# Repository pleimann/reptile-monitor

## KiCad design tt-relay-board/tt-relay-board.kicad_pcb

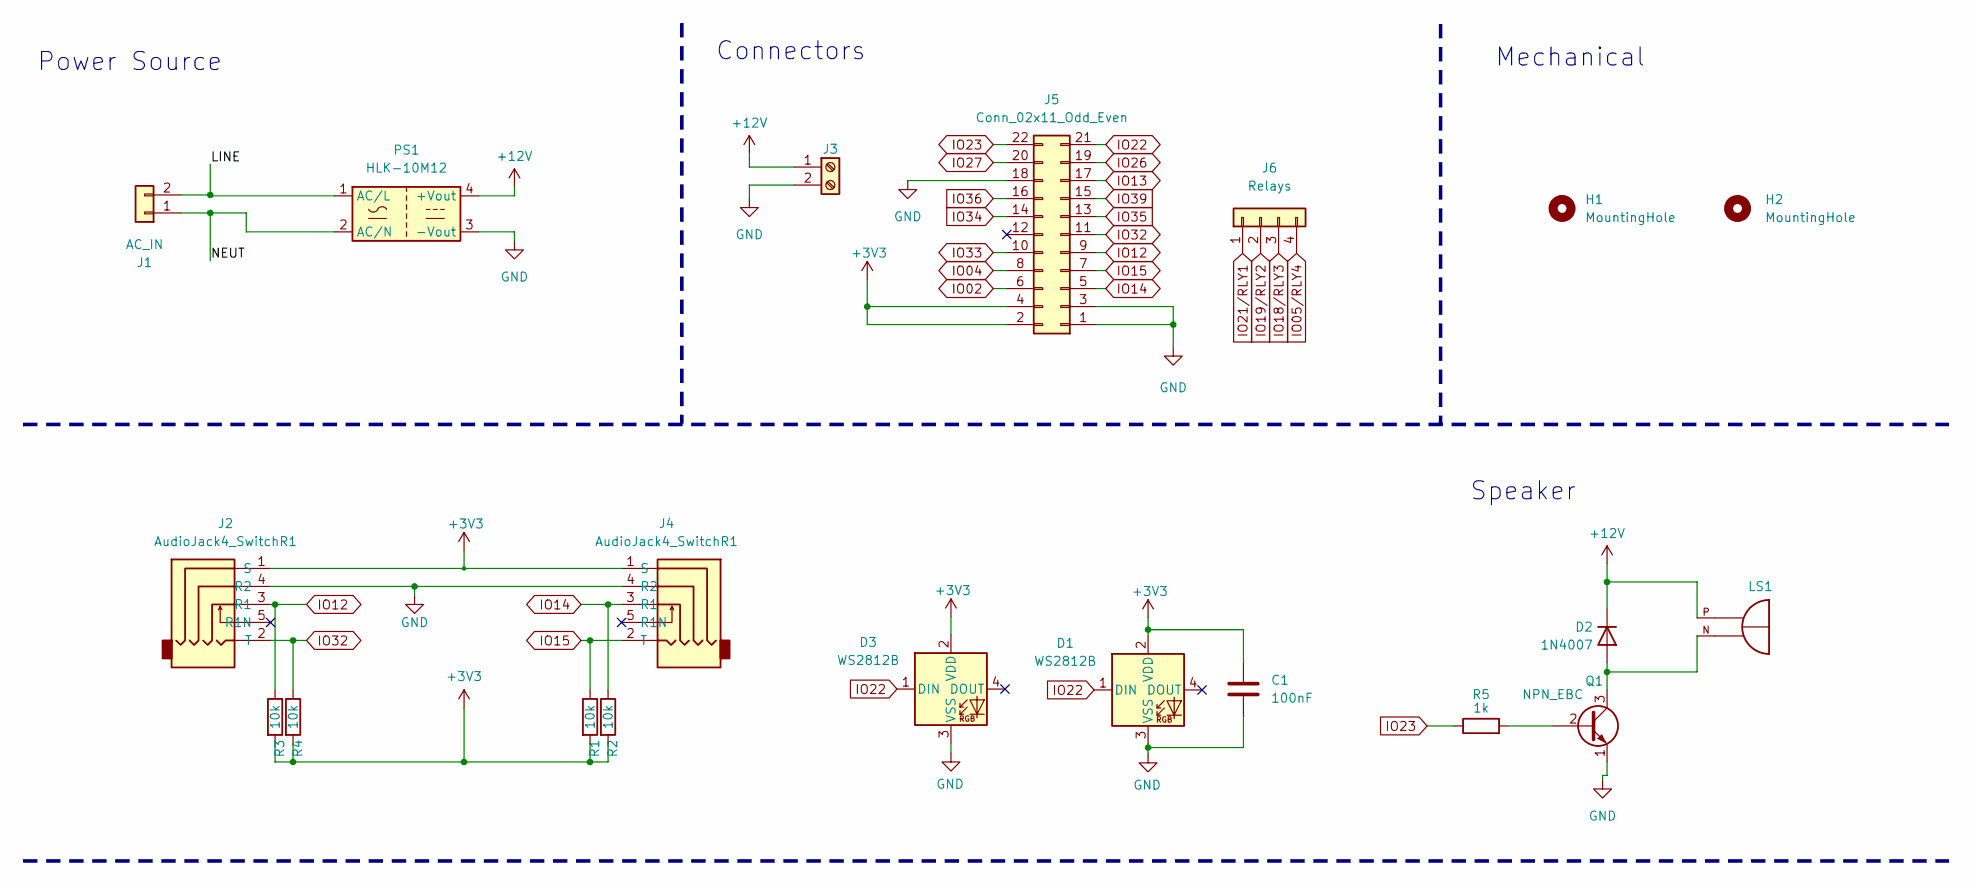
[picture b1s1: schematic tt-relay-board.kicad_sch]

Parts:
C1: 100nF; C_0603_1608Metric_Pad1.08x0.95mm_HandSolder
D1: WS2812B; LED_D5.0mm-4_RGB_Wide_Pins
D2: 1N4007; D_SOD-123F
D3: WS2812B; LED_WS2812B_PLCC4_5.0x5.0mm_P3.2mm
H1, H2: MountingHole; MountingHole_4mm
J1: AC_IN; SolderWire-0.75sqmm_1x02_P7mm_D1.25mm_OD3.5mm_Relief
J2, J4: AudioJack4_SwitchR1; Korean Hroparts Elec PJ-227-5A; LCSC Part C145819
J3: Screw_Terminal_01x02; SHDR2W110P0X500_1X2_1000X1120X
J5: Conn_02x11_Odd_Even; PinSocket_2x11_P2.54mm_Vertical
J6: Relays
LS1: XDCR_KSSG1201-16; mouser part number 539-AST7525MATRQ; digikey description AUDIO MAGNETIC XDCR 2.5-4.5V SMD
PS1: HLK-10M12; Converter_ACDC_HiLink_HLK-10Mxx
Q1: NPN_EBC; SOT-23
R1, R2, R3, R4: 10k; R_0603_1608Metric_Pad0.98x0.95mm_HandSolder
R5: 1k; R_0603_1608Metric_Pad0.98x0.95mm_HandSolder

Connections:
+3V3: C1.1, D1.2 (VDD), D3.2 (VDD), J2.1 (S), J4.1 (S), J5.2, J5.4, R1.2, R2.2, R3.2, R4.2
+12V: D2.1 (K), J3.1, LS1.P, PS1.4 (+Vout)
/LINE: J1.2, PS1.1 (AC/L)
/NEUT: J1.1, PS1.2 (AC/N)
GND: C1.2, D1.3 (VSS), D3.3 (VSS), J2.4 (R2), J3.2, J4.4 (R2), J5.1, J5.3, J5.18, PS1.3 (-Vout), Q1.1 (E)
IO02: J5.6
IO04: J5.8
IO12: J2.3 (R1), J5.9, R3.1
IO13: J5.17
IO14: J4.3 (R1), J5.5, R2.1
IO15: J4.2 (T), J5.7, R1.1
IO22: D1.1 (DIN), D3.1 (DIN), J5.21
IO23: J5.22, R5.1
IO26: J5.19
IO27: J5.20
IO32: J2.2 (T), J5.11, R4.1
IO33: J5.10
IO34: J5.14
IO35: J5.13
IO36: J5.16
IO39: J5.15
unnamed: D2.2 (A), LS1.N, Q1.3 (C)
unnamed: Q1.2 (B), R5.2

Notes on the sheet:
Power Source
Speaker
Mechanical
Connectors

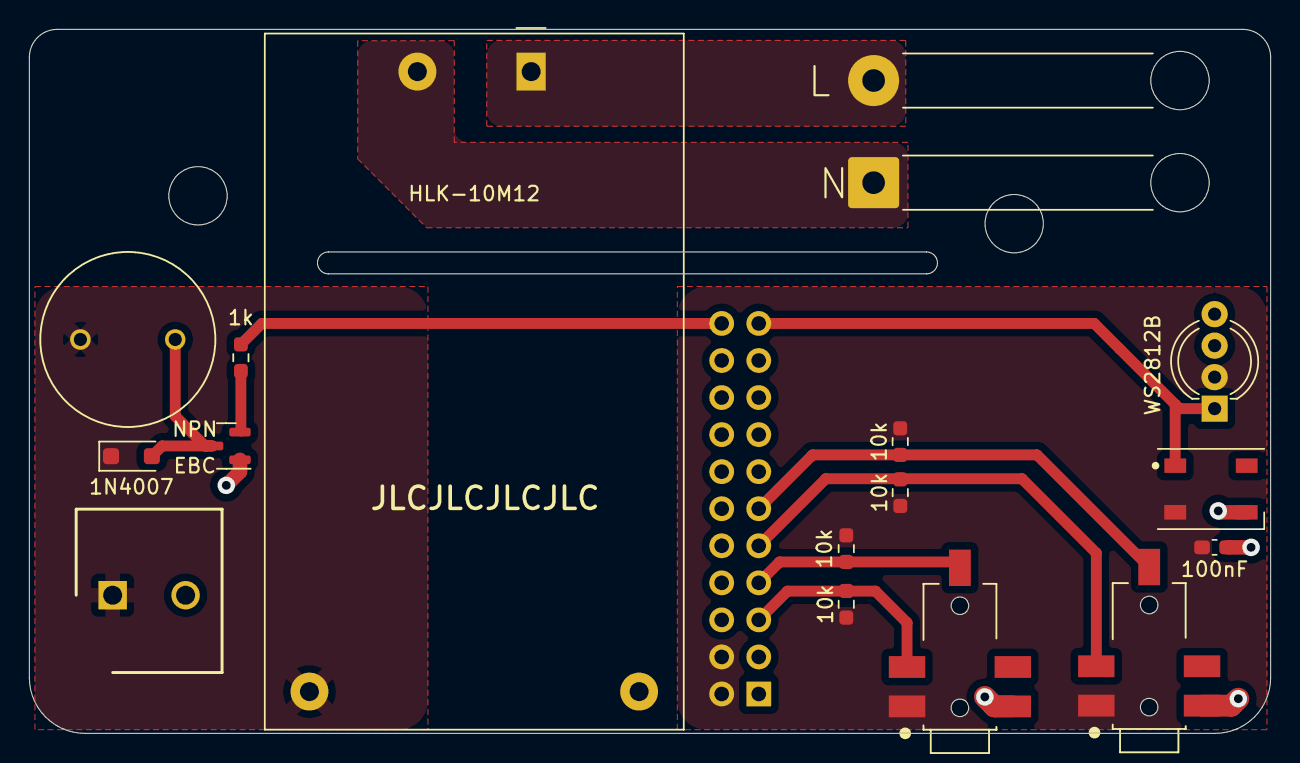
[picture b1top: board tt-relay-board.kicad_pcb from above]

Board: 2 copper layers, 85.1 x 48.3 mm, 19 parts (1 on the bottom side), 13 nets.

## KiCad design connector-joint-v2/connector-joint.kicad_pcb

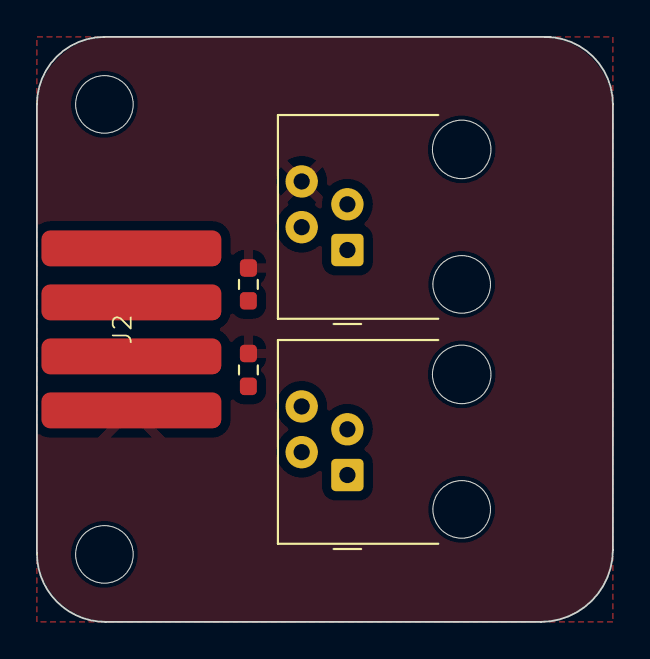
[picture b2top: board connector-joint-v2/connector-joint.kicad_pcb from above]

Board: 2 copper layers, 32.0 x 32.5 mm, 7 parts (0 on the bottom side), 4 nets, no tracks yet.

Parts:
H1, H2: MountingHole; MountingHole_3.2mm_M3
J2: Conn_01x04; SolderPad_x4
J4, J5: 4P4C; RJ9_Evercom_5301-440xxx_Horizontal
R1, R2: R_US; R_0603_1608Metric_Pad0.98x0.95mm_HandSolder

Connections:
+3V3: J2.4 (3V3), J4.3, J5.2
GND: J2.3 (GND), J4.2, J5.3, R2.2
unnamed: J2.1 (DATA), J4.4, R1.1, R2.1
unnamed: J2.2 (DATA), J4.1, J5.4, R1.2

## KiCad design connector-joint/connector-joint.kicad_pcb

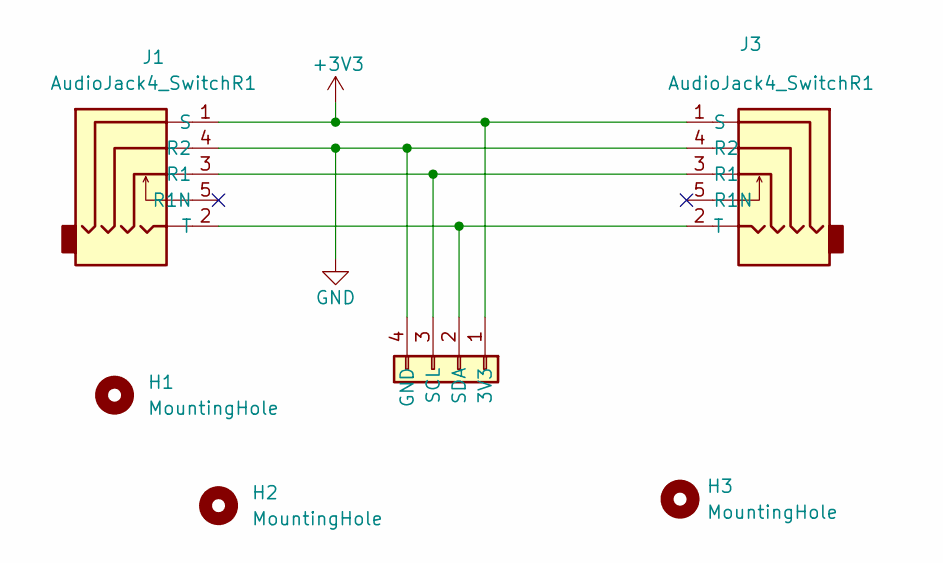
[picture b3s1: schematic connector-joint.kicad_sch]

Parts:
H1, H2, H3: MountingHole; MountingHole_3.2mm_M3
J1, J3: AudioJack4_SwitchR1; Korean Hroparts Elec PJ-227-5A; LCSC Part C145819
J2: Conn_01x04; SolderWire-0.15sqmm_1x04_P4mm_D0.5mm_OD1.5mm

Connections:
+3V3: J1.1 (S), J2.1, J3.1 (S)
GND: J1.4 (R2), J2.4, J3.4 (R2)
unnamed: J1.2 (T), J2.2, J3.2 (T)
unnamed: J1.3 (R1), J2.3, J3.3 (R1)

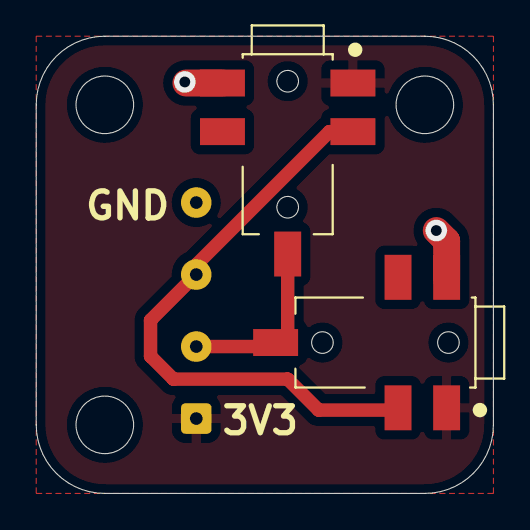
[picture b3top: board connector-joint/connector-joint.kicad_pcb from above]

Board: 2 copper layers, 25.4 x 25.4 mm, 6 parts (0 on the bottom side), 4 nets.

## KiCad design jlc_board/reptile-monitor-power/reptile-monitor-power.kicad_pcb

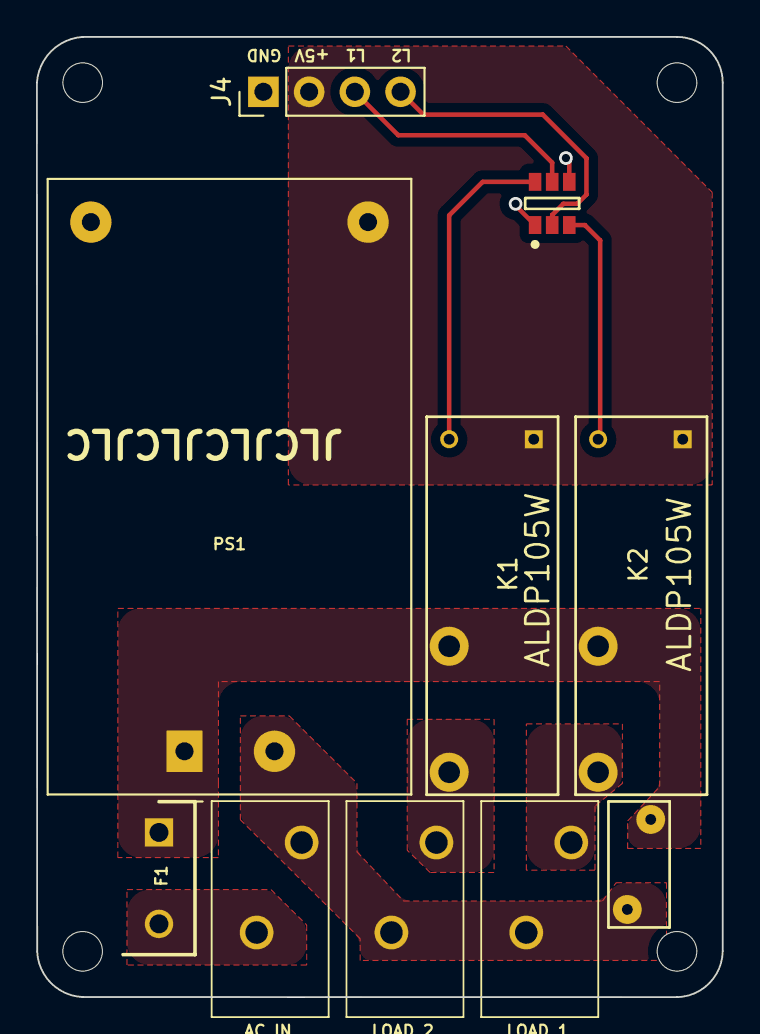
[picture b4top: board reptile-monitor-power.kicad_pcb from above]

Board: 4 copper layers, 38.1 x 53.3 mm, 14 parts (0 on the bottom side), 11 nets.

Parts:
F1: 39208000440; TO508P400X850X850-2P
J1: AC_IN; TE Connectivity PC Terminal Block 128340212
J2: LOAD_2; TE Connectivity PC Terminal Block 128340212
J3: LOAD_1; TE Connectivity PC Terminal Block 128340212
J4: POWER CONN; PinHeader_1x04_P2.54mm_Vertical
K1, K2: ALDP105W; Panasonic-ALDP105W-Manufacturer_Recommended
PS1: HLK-PM01; Converter_ACDC_HiLink_HLK-PMxx
REF1, REF1#2, REF1#3, REF1#4: MountingHole_2.2mm_M2_ISO7380
RV1: Varistor; RV_Disc_D7mm_W3.4mm_P5mm
U1: NUD3105DMT1G; ON_Semi-318F-0-0-0

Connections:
+5V: J4.2, K1.1, K2.1, PS1.4 (+Vout)
/FUSED_AC_L: F1.1, K1.3 (COM), K2.3 (COM), PS1.1 (AC/L), RV1.2
/LOAD1: J3.2, K2.2 (NO)
/LOAD2: J2.2, K1.2 (NO)
GND: J4.1, PS1.3 (-Vout), U1.1 (1_Source), U1.4 (2_Source)
L1: J4.3, U1.5 (2_Gate)
L2: J4.4, U1.2 (1_Gate)
LINE: F1.2, J1.1
NEUT: J1.2, J2.1, J3.1, PS1.2 (AC/N), RV1.1
RLY1: K2.4, U1.3 (2_Drain)
RLY2: K1.4, U1.6 (1_Drain)

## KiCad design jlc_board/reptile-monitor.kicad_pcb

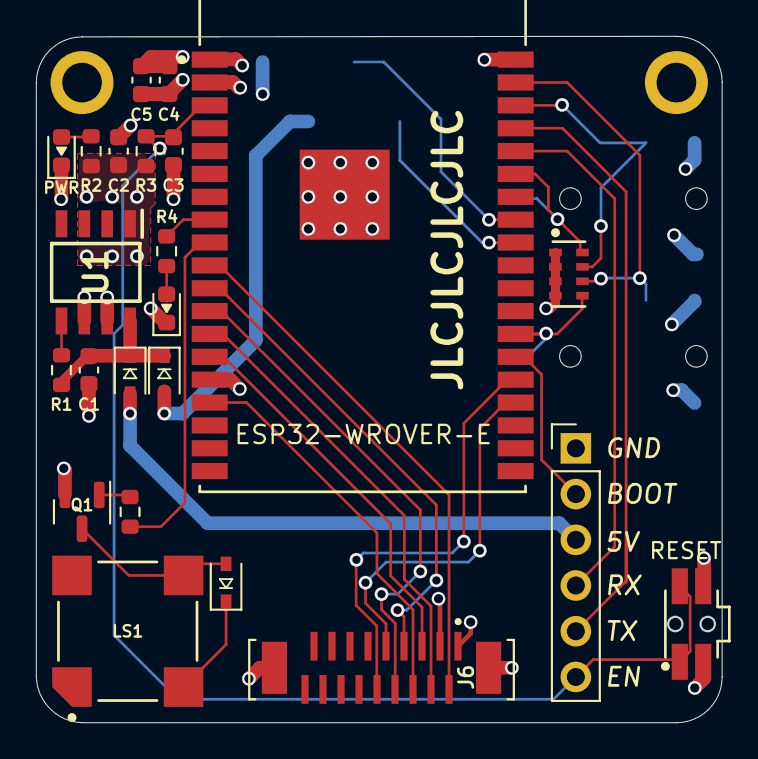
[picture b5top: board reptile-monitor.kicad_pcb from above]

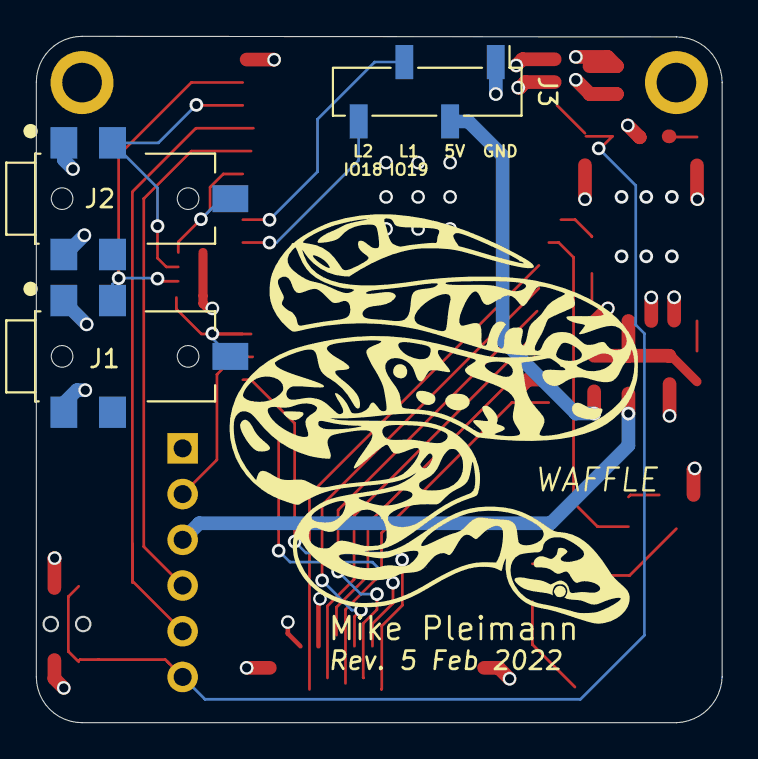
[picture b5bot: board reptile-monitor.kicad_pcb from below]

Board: 4 copper layers, 38.1 x 38.1 mm, 29 parts (4 on the bottom side), 31 nets.

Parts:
C1, C2: 1u; C_0603_1608Metric
C3, C5: 100n; C_0603_1608Metric
C4: 22u; C_0603_1608Metric
D1: PWR; LED_0603_1608Metric
D2: 32; LED_0603_1608Metric
D3, D4, D5: 1N4007; D_SOD-323
H1, H2: MountingHole; MountingHole_2.2mm_M2_ISO7380_Pad
J1, J2: AudioJack4_SwitchR1; Korean Hroparts Elec PJ-227-5A
J3: PWR CONN; PinSocket_1x04_P2.54mm_Vertical_SMD_Pin1Left
J4: UART; PinHeader_1x06_P2.54mm_Vertical
J6: 18-Lead FPC 0.5 mm - Vertical; TE_1-1734742-8
LS1: AST7525MATRQ; Mallory_Sonalert_Products_Inc-AST7525MATRQ-0-0-MFG
MD1: ESP32-WROVER-E; Espressif_Systems-ESP32-WROVER-0-0-MFG
Q1: Q_NPN_BEC; SOT-23
R1, R2, R3: 10k; R_0603_1608Metric
R4: 1k; R_0603_1608Metric
R5: 1K; R_0603_1608Metric
RN1: 10k; Panasonic-EXB-V8V103JV-0
SW1: RESET; Panasonic-EVQ-P7A01P
U1: AP2112M-3.3; SOIC127P600X170-8N
WAFFLE: LOGO

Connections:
+3V3: C2.2, C4.1, C5.1, J1.1 (S), J2.1 (S), J6.1, MD1.2 (VDD33), R2.1, R3.2, RN1.1 (R1.1), RN1.2 (R2.1), RN1.3 (R3.1), RN1.4 (R4.1), U1.1 (VOUT)
+5V: C1.1, D4.1 (K), D5.1 (K), R1.2, U1.8 (VIN)
/LED: MD1.8 (IO32), R4.2
/PWR_EN: R1.1, U1.5 (EN)
BK_LT: J6.2, MD1.10 (IO25)
BOOT: J4.2, MD1.25 (IO0)
BUZZER: MD1.9 (IO33), R5.1
DS_0: J1.3 (R1), MD1.37 (IO23), RN1.6 (R3.2)
DS_DATA: J1.2 (T), MD1.26 (IO4), RN1.5 (R4.2)
EN: C3.2, J4.6, MD1.3 (EN), R3.1, SW1.1, SW1.1'
GND: C1.2, C2.1, C3.1, C4.2, C5.2, D1.1 (K), D2.1 (K), H1.1, H2.1, J1.4 (R2), J2.4 (R2), J3.1, J4.1, J6.3, J6.S1 (SHIELD), J6.S2 (SHIELD), MD1.1 (GND), MD1.15 (GND), MD1.38 (GND), MD1.39 (GND), Q1.2 (E), SW1.2, SW1.2', U1.6 (GND_1), U1.7 (GND_2)
L1: J3.3, MD1.31 (IO19)
L2: J3.4, MD1.30 (IO18)
unnamed: D1.2 (A), R2.2
unnamed: D2.2 (A), R4.1
unnamed: D3.2 (A), LS1.4 (-), Q1.3 (C)
unnamed: D5.2 (A), J3.2
unnamed: D4.2 (A), J4.3
unnamed: Q1.1 (B), R5.2
RXD0: J4.4, MD1.34 (RXD0)
SCL0: J2.3 (R1), MD1.36 (IO22), RN1.7 (R2.2)
SDA0: J2.2 (T), MD1.33 (IO21), RN1.8 (R1.2)
SD_CS: J6.10, MD1.24 (IO2)
SPI_SCK: J6.4, MD1.13 (IO14)
SPI_SDI: J6.5, MD1.14 (IO12)
SPI_SDO: J6.6, MD1.16 (IO13)
TFT_CS: J6.9, MD1.23 (IO15)
TFT_DC: J6.7, MD1.11 (IO26)
TFT_RST: J6.8, MD1.12 (IO27)
TXD0: J4.5, MD1.35 (TXD0)
VDD: D3.1 (K), LS1.3 (+)

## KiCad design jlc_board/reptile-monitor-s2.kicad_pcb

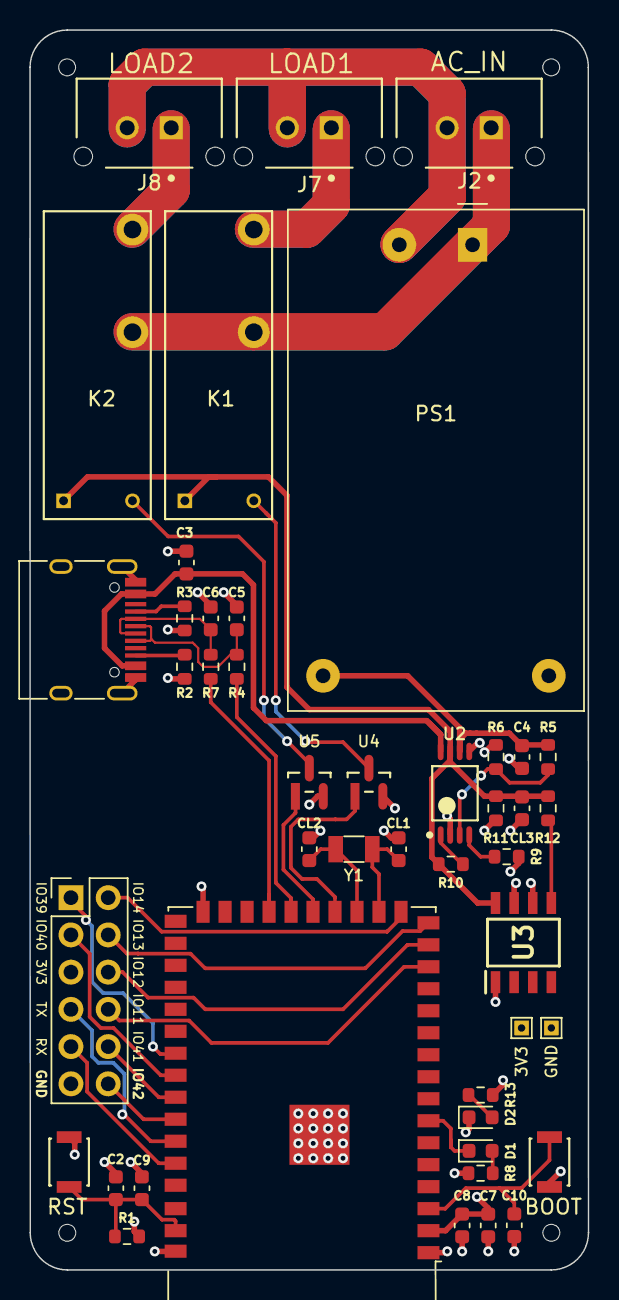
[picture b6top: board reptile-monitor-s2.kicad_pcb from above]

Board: 4 copper layers, 38.1 x 84.6 mm, 45 parts (0 on the bottom side), 40 nets.

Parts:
C2, C3, C4, C7, C9, C10: 0.1u; C_0603_1608Metric
C5, C6: 20p; C_0603_1608Metric
C8: 22u; C_0603_1608Metric
CL1, CL2: 20p; C_0603_1608Metric
CL3: 10u; C_0603_1608Metric
D1, D2: LED; LED_0603_1608Metric
J1: USB_C_Receptacle_USB2.0; USB_C_Receptacle_HRO_TYPE-C-31-M-12
J2: AC_IN; Molex-43650-0215-0-0-MFG
J3: Conn_01x08; PinHeader_2x06_P2.54mm_Vertical
J7: LOAD1; Molex-43650-0215-0-0-MFG
J8: LOAD2; Molex-43650-0215-0-0-MFG
K1, K2: ALDP105W; Panasonic-ALDP105W-Manufacturer_Recommended
PS1: HLK-PM01; Converter_ACDC_HiLink_HLK-PMxx
R1, R10, R11, R12: 10k; R_0603_1608Metric
R2, R3: 5.1k; R_0603_1608Metric
R4, R7: 22r; R_0603_1608Metric
R5: 2.2k; R_0603_1608Metric
R6: 1k; R_0603_1608Metric
R8, R13: 100r; R_0603_1608Metric
R9: 500r; R_0603_1608Metric
SW1: RST; Omron-B3U-1000P-MFG
SW2: BOOT; Omron-B3U-1000P-MFG
TP1: 3V3; TestPoint_THTPad_1.0x1.0mm_Drill0.5mm
TP3: GND; TestPoint_THTPad_1.0x1.0mm_Drill0.5mm
U1: ESP32-S2-WROVER
U2: TPS2112PW; Texas_Instruments-TPS2112PW
U3: AP2112K-3.3; SOIC127P600X170-8N
U4, U5: MDC3105LT1G; ON_Semiconductor-318-08-01_2018-AS
Y1: 32.768KHz 12.5p; Crystal_SMD_3215-2Pin_3.2x1.5mm

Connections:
+3V3: C7.1, C8.1, J3.5, R1.1, R13.1, TP1.1, U1.2 (3V3), U3.1 (VOUT)
+5V: CL3.1, K1.1, K2.1, R10.2, R11.2, R12.2, U2.7 (OUT), U3.8 (VIN)
/AC_L: J2.1, K1.3 (COM), K2.3 (COM), PS1.1 (AC/L)
/AC_N: J2.2, J7.2, J8.2, PS1.2 (AC/N)
/EN: C2.1, C9.1, R1.2, SW1.1, U1.41 (EN)
/IO0: C10.1, SW2.1, U1.3 (IO00)
/IO11: J3.8, U1.14 (IO11)
/IO12: J3.6, U1.15 (IO12)
/IO13: J3.4, U1.16 (IO13)
/IO14: J3.2, U1.17 (IO14)
/IO15: CL1.1, U1.18 (IO15), Y1.2
/IO16: CL2.1, U1.19 (IO16), Y1.1
/IO17: U1.20 (IO17), U4.1 (Vin)
/IO18: U1.21 (IO18), U5.1 (Vin)
/IO39: J3.1, U1.33 (IO39)
/IO40: J3.3, U1.34 (IO40)
/IO41: J3.10, U1.35 (IO41)
/IO42: J3.12, U1.36 (IO42)
/LOAD1: J7.1, K1.2 (NO)
/LOAD2: J8.1, K2.2 (NO)
/PWR_SRC: R10.1, U2.1 (STAT)
/RXD0: J3.9, U1.38 (RXD0)
/TXD0: J3.7, U1.37 (TXD0)
/USB_D+: C5.2, J1.A6 (D+), J1.B6 (D+), R4.1
/USB_D-: C6.1, J1.A7 (D-), J1.B7 (D-), R7.1
GND: C2.2, C3.2, C4.2, C5.1, C6.2, C7.2, C8.2, C9.2, C10.2, CL1.2, CL2.2, CL3.2, D2.1 (K), J1.A1 (GND), J1.A12 (GND), J1.B1 (GND), J1.B12 (GND), J1.S1 (SHIELD), J3.11, PS1.3 (-Vout), R2.2, R3.2, R6.2, R8.2, R9.1, R11.1, SW1.2, SW2.2, TP3.1, U1.1 (GND), U1.26 (GND), U1.42 (GND), U1.43 (GND), U2.2 (~EN~), U2.5 (GND), U3.6 (GND_1), U3.7 (GND_2), U4.2 (GND), U5.2 (GND)
unnamed: D1.1 (K), U1.7 (IO04)
unnamed: D1.2 (A), R8.1
unnamed: D2.2 (A), R13.2
unnamed: J1.A5 (CC1), R3.1
unnamed: J1.B5 (CC2), R2.1
unnamed: K2.4, U5.3 (Vout)
unnamed: R4.2, U1.22 (USB_D-)
unnamed: R5.2, R6.1, U2.3 (VSNS)
unnamed: R7.2, U1.23 (USB_D+)
unnamed: R9.2, U2.4 (ILIM)
unnamed: R12.1, U3.5 (EN)
unnamed: K1.4, U4.3 (Vout)
VBUS: C3.1, J1.A4 (VBUS), J1.A9 (VBUS), J1.B4 (VBUS), J1.B9 (VBUS), U2.8 (IN1)
VCC: C4.1, PS1.4 (+Vout), R5.1, U2.6 (IN2)

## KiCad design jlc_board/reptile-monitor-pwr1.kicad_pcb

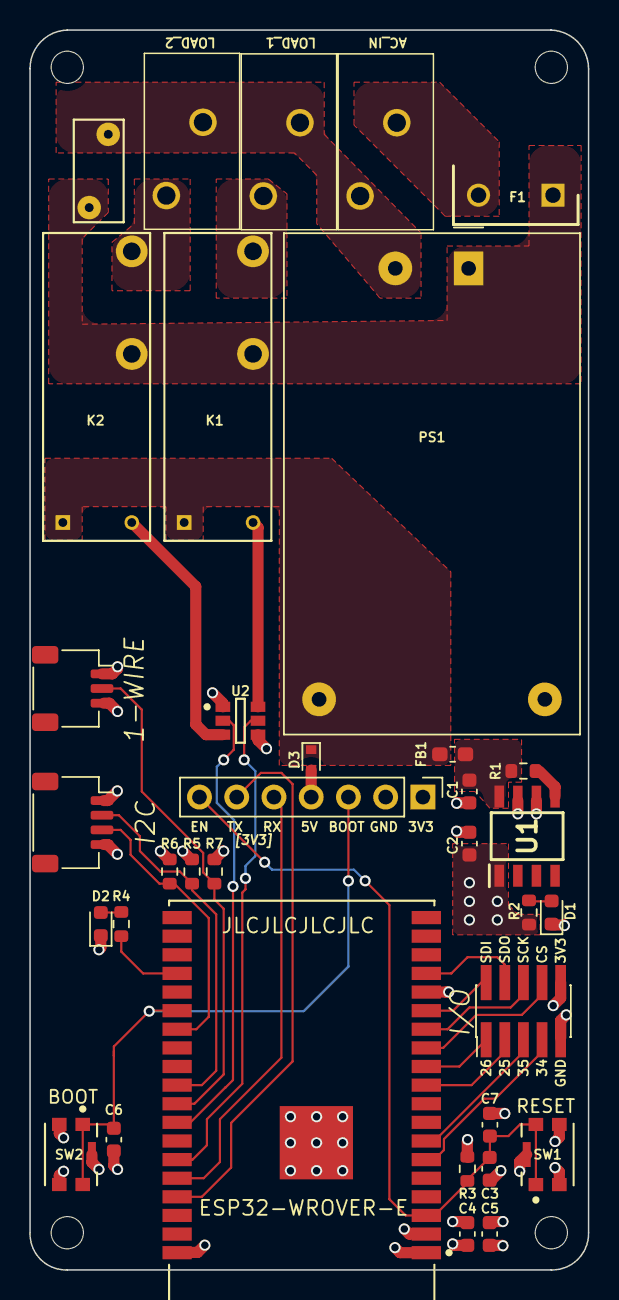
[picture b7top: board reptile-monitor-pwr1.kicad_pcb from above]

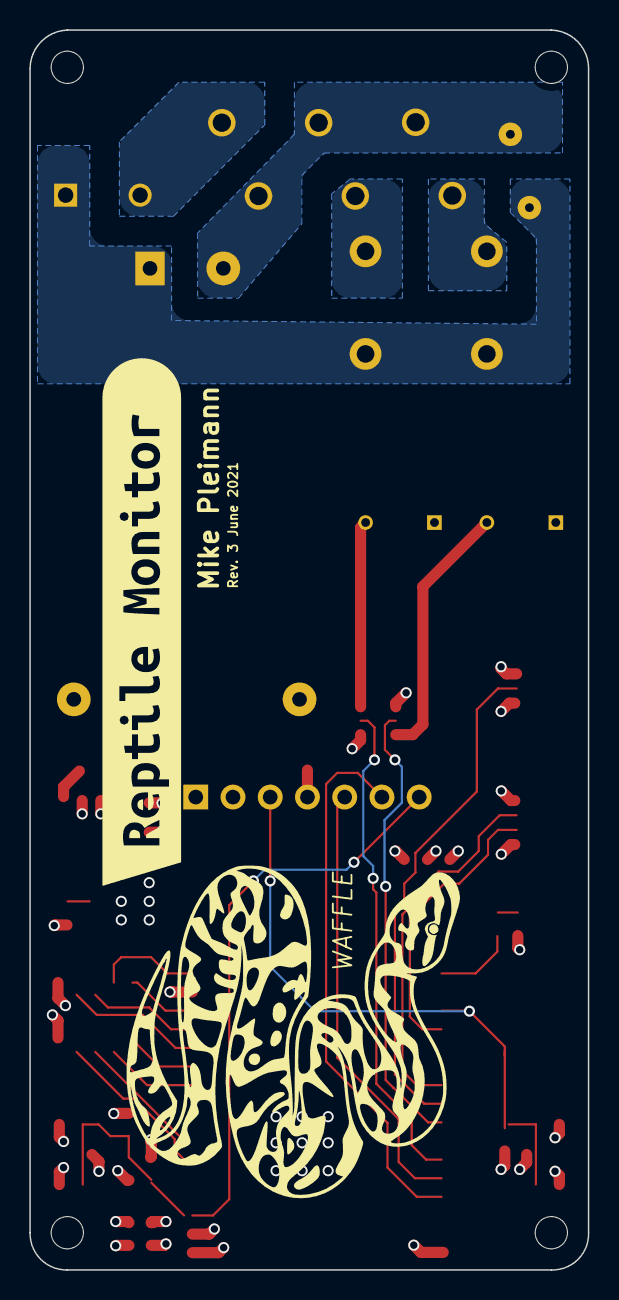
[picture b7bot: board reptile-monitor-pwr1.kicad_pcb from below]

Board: 4 copper layers, 38.1 x 84.6 mm, 41 parts (2 on the bottom side), 33 nets.

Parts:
C1, C2: 1u; C_0603_1608Metric
C3, C5, C6, C7: 100n; C_0603_1608Metric
C4: 22u; C_0603_1608Metric
D1: RED; LED_0603_1608Metric
D2: BLUE; LED_0603_1608Metric
D3: Schottky; D_SOD-523
F1: 39208000440; TO508P400X850X850-2P
FB1: 360 m; L_0603_1608Metric_Pad1.05x0.95mm_HandSolder
J1: 1-WIRE; JST_SH_SM03B-SRSS-TB_1x03-1MP_P1.00mm_Horizontal
J2: UART; PinHeader_1x07_P2.54mm_Vertical
J3: AC_IN; 128340212
J4: LOAD_1; 128340212
J5: LOAD_2; 128340212
J6: I/O; PinHeader_2x05_P1.27mm_Vertical_SMD
J8: I2C; JST_SH_SM04B-SRSS-TB_1x04-1MP_P1.00mm_Horizontal
K1, K2: ALDP105W; Panasonic-ALDP105W-Manufacturer_Recommended
MD1: ESP32-WROVER-E; Espressif_Systems-ESP32-WROVER-0-0-MFG
PS1: HLK-PM01; Converter_ACDC_HiLink_HLK-PMxx
R1, R2, R3, R4, R5, R6, R7: 10k; R_0603_1608Metric
REF1, REF1#2, REF1#3, REF1#4: MountingHole_2.2mm_M2_ISO7380
RV1: Varistor; RV_Disc_D7mm_W3.4mm_P5mm
SW1: RESET; CK-KMR221GLFS-MFG
SW2: BOOT; CK-KMR221GLFS-MFG
U1: AP2112M-3.3; SOIC127P600X170-8N
U2: NUD3105DMT1G; ON_Semi-318F-0-0-0
WAFFLE: LOGO
svg2mod: G***; svg2mod

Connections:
1-WIRE: J1.2, MD1.30 (IO18), R7.2
+3V3: C2.2, C4.1, C5.1, J1.3, J2.1, J6.10, J8.1, MD1.2 (VDD33), R2.1, R3.2, R5.1, R6.1, R7.1, U1.1 (VOUT)
+5V: D3.1 (K), FB1.1, K1.1, K2.1, PS1.4 (+Vout)
/AC_L: F1.2, J3.1
/AC_N: J3.2, J4.1, J5.1, PS1.2 (AC/N), RV1.1
/EN: C3.1, C7.1, J2.7, MD1.3 (EN), R3.1, SW1.1, SW1.2
/FUSED_AC_L: F1.1, K1.3 (COM), K2.3 (COM), PS1.1 (AC/L), RV1.2
/LED: MD1.23 (IO15), R4.2
/LOAD1: J4.2, K1.2 (NO)
/LOAD2: J5.2, K2.2 (NO)
/PWR_EN: R1.1, U1.5 (EN)
/RLY1: K1.4, U2.6 (1_Drain)
/RLY2: K2.4, U2.3 (2_Drain)
BOOT: C6.1, J2.3, MD1.25 (IO0), SW2.1, SW2.2
CS0: J6.8, MD1.12 (IO27)
GND: C1.2, C2.1, C3.2, C4.2, C5.2, C6.2, C7.2, D1.1 (K), D2.1 (K), J1.1, J2.2, J6.9, J8.4, MD1.1 (GND), MD1.15 (GND), MD1.38 (GND), MD1.39 (GND), PS1.3 (-Vout), SW1.3, SW1.4, SW1.5 (GROUND), SW2.3, SW2.4, SW2.5 (GROUND), U1.6 (GND_1), U1.7 (GND_2), U2.1 (1_Source), U2.4 (2_Source)
IO25: J6.3, MD1.10 (IO25)
IO26: J6.1, MD1.11 (IO26)
IO34: J6.7, MD1.6 (IO34)
IO35: J6.5, MD1.7 (IO35)
L1: MD1.31 (IO19), U2.2 (1_Gate)
L2: MD1.33 (IO21), U2.5 (2_Gate)
unnamed: C1.1, FB1.2, R1.2, U1.8 (VIN)
unnamed: D1.2 (A), R2.2
unnamed: D2.2 (A), R4.1
unnamed: D3.2 (A), J2.4
RXD0: J2.5, MD1.34 (RXD0)
SCK: J6.6, MD1.13 (HSPI_SCK)
SCL: J8.3, MD1.26 (IO4), R6.2
SDA: J8.2, MD1.29 (IO5), R5.2
SDI: J6.2, MD1.14 (HSPI_SDI)
SDO: J6.4, MD1.16 (HSPI_SDO)
TXD0: J2.6, MD1.35 (TXD0)

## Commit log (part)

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2021-03-12 add enclosure controllers
2021-04-18 JLC Board V1.0
2021-04-22 Rev2 - Change to Panasonic relays as they're actually attainable and cheaper.
2021-04-22 Change ALPS to Omron boot and reset buttons cause they're available from Digi-Key
2021-05-02 rev2
2021-05-09 rev 2
2021-05-19 Rev2 - Waffle & Wesley
2021-05-19 move ibom to board dir
2021-06-11 Revision 3
2021-07-04 separate power board
2021-07-23 Rev 3 - separate power board
2021-08-05 consolidate kicad libraries
2021-08-20 rev4
2021-08-21 move quiic connector to same side as TRRS sensor connectors so that all connectors are on the same side
2021-09-03 v4 reorganization complete
2021-09-07 add rev4 ibom
2021-09-07 add raight angle tactile switch
2021-10-16 Change LED value to remove IO5 confusion
2021-10-17 notes
2021-10-17 rev4.5
2021-11-14 update 3d model
2021-12-04 dunno
2021-12-09 Eliminate I2C Chip & move stemma qt connector to top
2021-12-09 change blu led to 1k resistor so it's brighter
2022-04-24 rev5
2023-07-17 tt-relay
2023-08-04 Fix component positions in tt-relay-board
